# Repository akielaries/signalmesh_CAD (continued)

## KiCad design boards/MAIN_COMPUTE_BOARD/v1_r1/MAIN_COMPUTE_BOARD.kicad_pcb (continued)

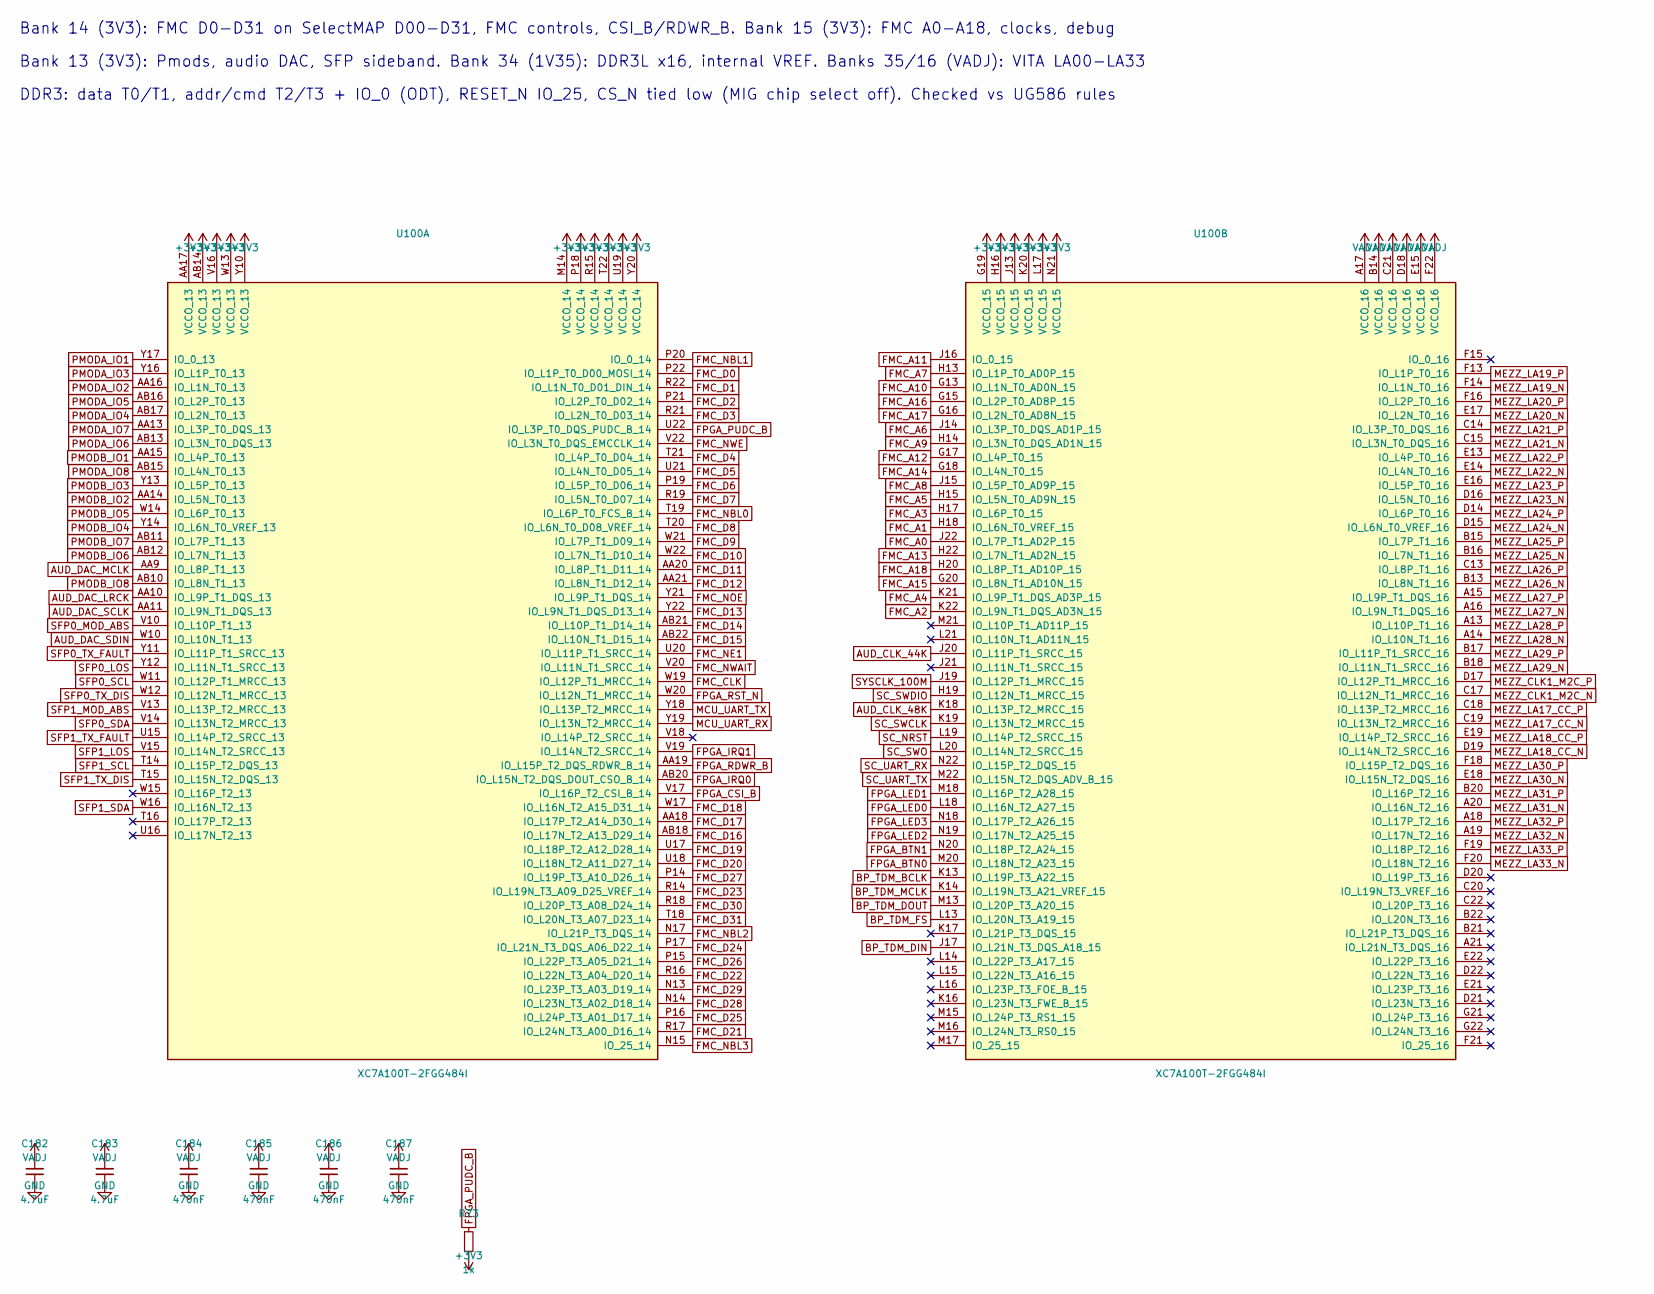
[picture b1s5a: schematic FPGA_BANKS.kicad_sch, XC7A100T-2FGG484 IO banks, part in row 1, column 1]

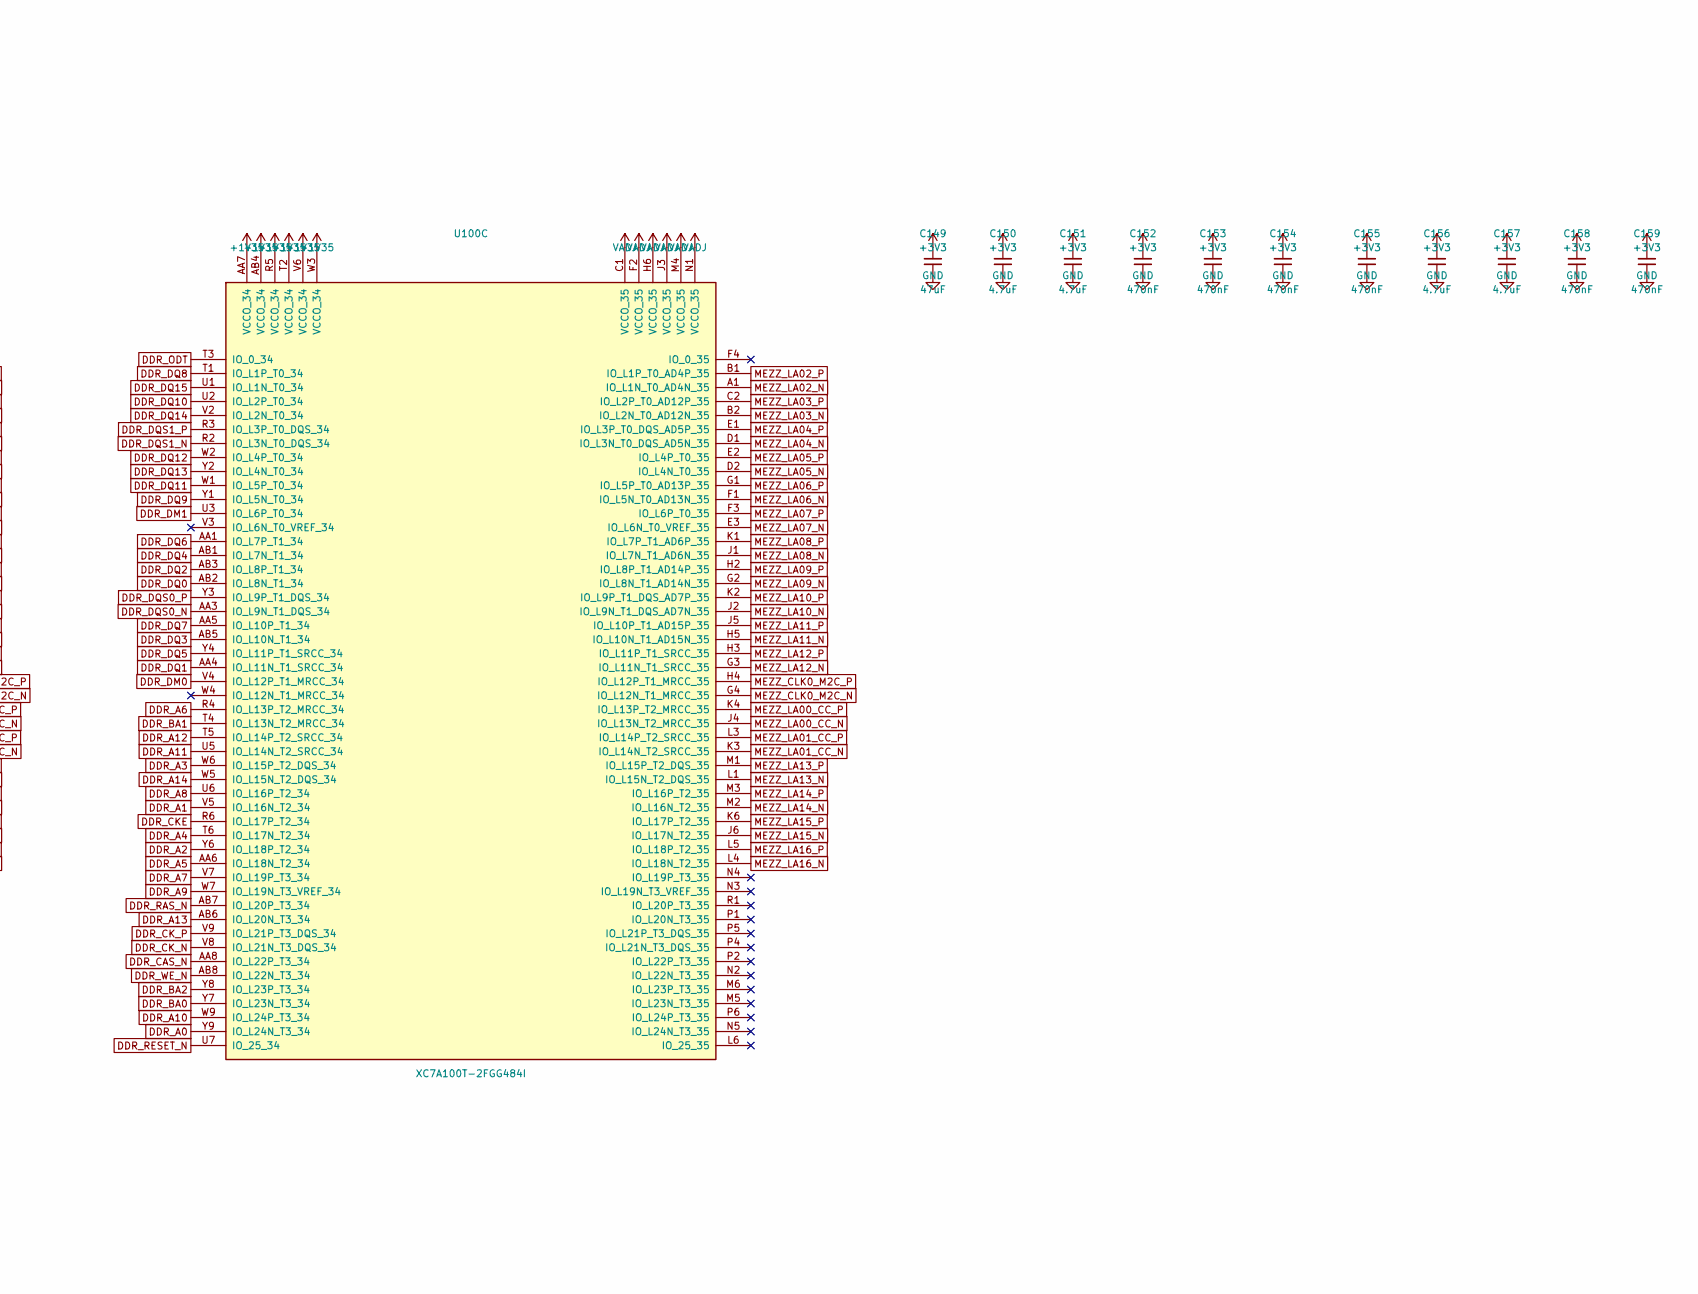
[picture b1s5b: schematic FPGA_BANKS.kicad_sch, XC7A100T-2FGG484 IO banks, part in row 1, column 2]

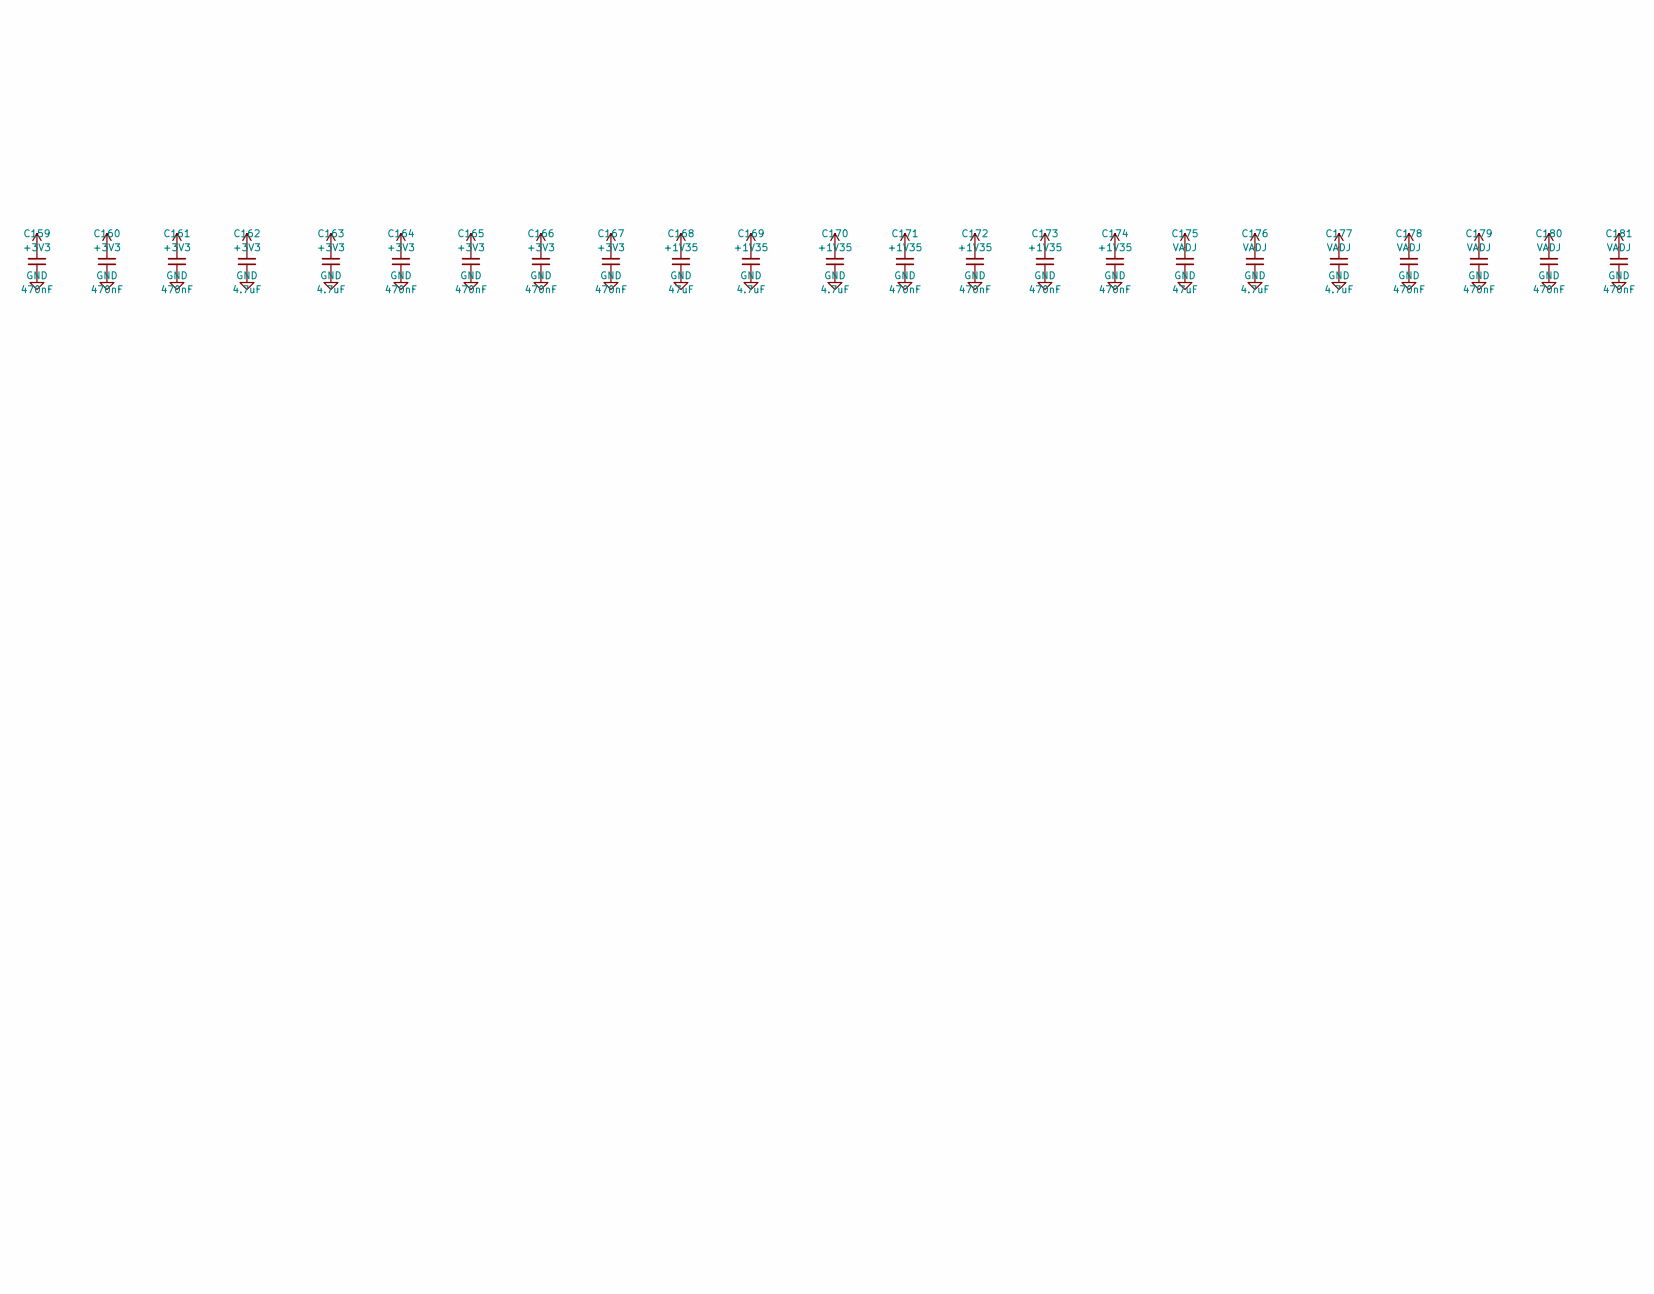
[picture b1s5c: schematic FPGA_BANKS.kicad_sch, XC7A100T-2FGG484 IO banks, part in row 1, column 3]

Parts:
C149, C168, C175: 47uF; C_1206_3216Metric
C150, C151, C156, C157, C162, C163, C169, C170, C176, C177, C182, C183: 4.7uF; C_0603_1608Metric
C152, C153, C154, C155, C158, C159, C160, C161, C164, C165, C166, C167, C171, C172, C173, C174, C178, C179, C180, C181, C184, C185, C186, C187: 470nF; C_0402_1005Metric
R73: 1k; R_0402_1005Metric
U100: XC7A100T-2FGG484I; Xilinx_FGG484

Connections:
+1V35: C168.1, C169.1, C170.1, C171.1, C172.1, C173.1, C174.1, U100.AA7 (VCCO_34), U100.AB4 (VCCO_34), U100.R5 (VCCO_34), U100.T2 (VCCO_34), U100.V6 (VCCO_34), U100.W3 (VCCO_34); also elsewhere on the board
+3V3: C149.1, C150.1, C151.1, C152.1, C153.1, C154.1, C155.1, C156.1, C157.1, C158.1, C159.1, C160.1, C161.1, C162.1, C163.1, C164.1, C165.1, C166.1, C167.1, R73.2, U100.AA17 (VCCO_13), U100.AB14 (VCCO_13), U100.G19 (VCCO_15), U100.H16 (VCCO_15), U100.J13 (VCCO_15), U100.K20 (VCCO_15), U100.L17 (VCCO_15), U100.M14 (VCCO_14), U100.N21 (VCCO_15), U100.P18 (VCCO_14), U100.R15 (VCCO_14), U100.T22 (VCCO_14), U100.U19 (VCCO_14), U100.V16 (VCCO_13), U100.W13 (VCCO_13), U100.Y10 (VCCO_13), U100.Y20 (VCCO_14); also elsewhere on the board
AUD_CLK_44K: U100.J20 (IO_L11P_T1_SRCC_15); also elsewhere on the board
AUD_CLK_48K: U100.K18 (IO_L13P_T2_MRCC_15); also elsewhere on the board
AUD_DAC_LRCK: U100.AA10 (IO_L9P_T1_DQS_13); also elsewhere on the board
AUD_DAC_MCLK: U100.AA9 (IO_L8P_T1_13); also elsewhere on the board
AUD_DAC_SCLK: U100.AA11 (IO_L9N_T1_DQS_13); also elsewhere on the board
AUD_DAC_SDIN: U100.W10 (IO_L10N_T1_13); also elsewhere on the board
BP_TDM_BCLK: U100.K13 (IO_L19P_T3_A22_15); also elsewhere on the board
BP_TDM_DIN: U100.J17 (IO_L21N_T3_DQS_A18_15); also elsewhere on the board
BP_TDM_DOUT: U100.M13 (IO_L20P_T3_A20_15); also elsewhere on the board
BP_TDM_FS: U100.L13 (IO_L20N_T3_A19_15); also elsewhere on the board
BP_TDM_MCLK: U100.K14 (IO_L19N_T3_A21_VREF_15); also elsewhere on the board
DDR_A0: U100.Y9 (IO_L24N_T3_34); also elsewhere on the board
DDR_A1: U100.V5 (IO_L16N_T2_34); also elsewhere on the board
DDR_A2: U100.Y6 (IO_L18P_T2_34); also elsewhere on the board
DDR_A3: U100.W6 (IO_L15P_T2_DQS_34); also elsewhere on the board
DDR_A4: U100.T6 (IO_L17N_T2_34); also elsewhere on the board
DDR_A5: U100.AA6 (IO_L18N_T2_34); also elsewhere on the board
DDR_A6: U100.R4 (IO_L13P_T2_MRCC_34); also elsewhere on the board
DDR_A7: U100.V7 (IO_L19P_T3_34); also elsewhere on the board
DDR_A8: U100.U6 (IO_L16P_T2_34); also elsewhere on the board
DDR_A9: U100.W7 (IO_L19N_T3_VREF_34); also elsewhere on the board
DDR_A10: U100.W9 (IO_L24P_T3_34); also elsewhere on the board
DDR_A11: U100.U5 (IO_L14N_T2_SRCC_34); also elsewhere on the board
DDR_A12: U100.T5 (IO_L14P_T2_SRCC_34); also elsewhere on the board
DDR_A13: U100.AB6 (IO_L20N_T3_34); also elsewhere on the board
DDR_A14: U100.W5 (IO_L15N_T2_DQS_34); also elsewhere on the board
DDR_BA0: U100.Y7 (IO_L23N_T3_34); also elsewhere on the board
DDR_BA1: U100.T4 (IO_L13N_T2_MRCC_34); also elsewhere on the board
DDR_BA2: U100.Y8 (IO_L23P_T3_34); also elsewhere on the board
DDR_CAS_N: U100.AA8 (IO_L22P_T3_34); also elsewhere on the board
DDR_CKE: U100.R6 (IO_L17P_T2_34); also elsewhere on the board
DDR_CK_N: U100.V8 (IO_L21N_T3_DQS_34); also elsewhere on the board
DDR_CK_P: U100.V9 (IO_L21P_T3_DQS_34); also elsewhere on the board
DDR_DM0: U100.V4 (IO_L12P_T1_MRCC_34); also elsewhere on the board
DDR_DM1: U100.U3 (IO_L6P_T0_34); also elsewhere on the board
DDR_DQ0: U100.AB2 (IO_L8N_T1_34); also elsewhere on the board
DDR_DQ1: U100.AA4 (IO_L11N_T1_SRCC_34); also elsewhere on the board
DDR_DQ2: U100.AB3 (IO_L8P_T1_34); also elsewhere on the board
DDR_DQ3: U100.AB5 (IO_L10N_T1_34); also elsewhere on the board
DDR_DQ4: U100.AB1 (IO_L7N_T1_34); also elsewhere on the board
DDR_DQ5: U100.Y4 (IO_L11P_T1_SRCC_34); also elsewhere on the board
DDR_DQ6: U100.AA1 (IO_L7P_T1_34); also elsewhere on the board
DDR_DQ7: U100.AA5 (IO_L10P_T1_34); also elsewhere on the board
DDR_DQ8: U100.T1 (IO_L1P_T0_34); also elsewhere on the board
DDR_DQ9: U100.Y1 (IO_L5N_T0_34); also elsewhere on the board
DDR_DQ10: U100.U2 (IO_L2P_T0_34); also elsewhere on the board
DDR_DQ11: U100.W1 (IO_L5P_T0_34); also elsewhere on the board
DDR_DQ12: U100.W2 (IO_L4P_T0_34); also elsewhere on the board
DDR_DQ13: U100.Y2 (IO_L4N_T0_34); also elsewhere on the board
DDR_DQ14: U100.V2 (IO_L2N_T0_34); also elsewhere on the board
DDR_DQ15: U100.U1 (IO_L1N_T0_34); also elsewhere on the board
DDR_DQS0_N: U100.AA3 (IO_L9N_T1_DQS_34); also elsewhere on the board
DDR_DQS0_P: U100.Y3 (IO_L9P_T1_DQS_34); also elsewhere on the board
DDR_DQS1_N: U100.R2 (IO_L3N_T0_DQS_34); also elsewhere on the board
DDR_DQS1_P: U100.R3 (IO_L3P_T0_DQS_34); also elsewhere on the board
DDR_ODT: U100.T3 (IO_0_34); also elsewhere on the board
DDR_RAS_N: U100.AB7 (IO_L20P_T3_34); also elsewhere on the board
DDR_RESET_N: U100.U7 (IO_25_34); also elsewhere on the board
DDR_WE_N: U100.AB8 (IO_L22N_T3_34); also elsewhere on the board
FMC_A0: U100.J22 (IO_L7P_T1_AD2P_15); also elsewhere on the board
FMC_A1: U100.H18 (IO_L6N_T0_VREF_15); also elsewhere on the board
FMC_A2: U100.K22 (IO_L9N_T1_DQS_AD3N_15); also elsewhere on the board
FMC_A3: U100.H17 (IO_L6P_T0_15); also elsewhere on the board
FMC_A4: U100.K21 (IO_L9P_T1_DQS_AD3P_15); also elsewhere on the board
FMC_A5: U100.H15 (IO_L5N_T0_AD9N_15); also elsewhere on the board
FMC_A6: U100.J14 (IO_L3P_T0_DQS_AD1P_15); also elsewhere on the board
FMC_A7: U100.H13 (IO_L1P_T0_AD0P_15); also elsewhere on the board
FMC_A8: U100.J15 (IO_L5P_T0_AD9P_15); also elsewhere on the board
FMC_A9: U100.H14 (IO_L3N_T0_DQS_AD1N_15); also elsewhere on the board
FMC_A10: U100.G13 (IO_L1N_T0_AD0N_15); also elsewhere on the board
FMC_A11: U100.J16 (IO_0_15); also elsewhere on the board
FMC_A12: U100.G17 (IO_L4P_T0_15); also elsewhere on the board
FMC_A13: U100.H22 (IO_L7N_T1_AD2N_15); also elsewhere on the board
FMC_A14: U100.G18 (IO_L4N_T0_15); also elsewhere on the board
FMC_A15: U100.G20 (IO_L8N_T1_AD10N_15); also elsewhere on the board
FMC_A16: U100.G15 (IO_L2P_T0_AD8P_15); also elsewhere on the board
FMC_A17: U100.G16 (IO_L2N_T0_AD8N_15); also elsewhere on the board
FMC_A18: U100.H20 (IO_L8P_T1_AD10P_15); also elsewhere on the board
FMC_CLK: U100.W19 (IO_L12P_T1_MRCC_14); also elsewhere on the board
FMC_D0: U100.P22 (IO_L1P_T0_D00_MOSI_14); also elsewhere on the board
FMC_D1: U100.R22 (IO_L1N_T0_D01_DIN_14); also elsewhere on the board
FMC_D2: U100.P21 (IO_L2P_T0_D02_14); also elsewhere on the board
FMC_D3: U100.R21 (IO_L2N_T0_D03_14); also elsewhere on the board
FMC_D4: U100.T21 (IO_L4P_T0_D04_14); also elsewhere on the board
FMC_D5: U100.U21 (IO_L4N_T0_D05_14); also elsewhere on the board
FMC_D6: U100.P19 (IO_L5P_T0_D06_14); also elsewhere on the board
FMC_D7: U100.R19 (IO_L5N_T0_D07_14); also elsewhere on the board
FMC_D8: U100.T20 (IO_L6N_T0_D08_VREF_14); also elsewhere on the board
FMC_D9: U100.W21 (IO_L7P_T1_D09_14); also elsewhere on the board
FMC_D10: U100.W22 (IO_L7N_T1_D10_14); also elsewhere on the board
FMC_D11: U100.AA20 (IO_L8P_T1_D11_14); also elsewhere on the board
FMC_D12: U100.AA21 (IO_L8N_T1_D12_14); also elsewhere on the board
FMC_D13: U100.Y22 (IO_L9N_T1_DQS_D13_14); also elsewhere on the board
FMC_D14: U100.AB21 (IO_L10P_T1_D14_14); also elsewhere on the board
FMC_D15: U100.AB22 (IO_L10N_T1_D15_14); also elsewhere on the board
FMC_D16: U100.AB18 (IO_L17N_T2_A13_D29_14); also elsewhere on the board
FMC_D17: U100.AA18 (IO_L17P_T2_A14_D30_14); also elsewhere on the board
FMC_D18: U100.W17 (IO_L16N_T2_A15_D31_14); also elsewhere on the board
FMC_D19: U100.U17 (IO_L18P_T2_A12_D28_14); also elsewhere on the board
FMC_D20: U100.U18 (IO_L18N_T2_A11_D27_14); also elsewhere on the board
FMC_D21: U100.R17 (IO_L24N_T3_A00_D16_14); also elsewhere on the board
FMC_D22: U100.R16 (IO_L22N_T3_A04_D20_14); also elsewhere on the board
FMC_D23: U100.R14 (IO_L19N_T3_A09_D25_VREF_14); also elsewhere on the board
FMC_D24: U100.P17 (IO_L21N_T3_DQS_A06_D22_14); also elsewhere on the board
FMC_D25: U100.P16 (IO_L24P_T3_A01_D17_14); also elsewhere on the board
FMC_D26: U100.P15 (IO_L22P_T3_A05_D21_14); also elsewhere on the board
FMC_D27: U100.P14 (IO_L19P_T3_A10_D26_14); also elsewhere on the board
FMC_D28: U100.N14 (IO_L23N_T3_A02_D18_14); also elsewhere on the board
FMC_D29: U100.N13 (IO_L23P_T3_A03_D19_14); also elsewhere on the board
FMC_D30: U100.R18 (IO_L20P_T3_A08_D24_14); also elsewhere on the board
FMC_D31: U100.T18 (IO_L20N_T3_A07_D23_14); also elsewhere on the board
FMC_NBL0: U100.T19 (IO_L6P_T0_FCS_B_14); also elsewhere on the board
FMC_NBL1: U100.P20 (IO_0_14); also elsewhere on the board
FMC_NBL2: U100.N17 (IO_L21P_T3_DQS_14); also elsewhere on the board
FMC_NBL3: U100.N15 (IO_25_14); also elsewhere on the board
FMC_NE1: U100.U20 (IO_L11P_T1_SRCC_14); also elsewhere on the board
FMC_NOE: U100.Y21 (IO_L9P_T1_DQS_14); also elsewhere on the board
FMC_NWAIT: U100.V20 (IO_L11N_T1_SRCC_14); also elsewhere on the board
FMC_NWE: U100.V22 (IO_L3N_T0_DQS_EMCCLK_14); also elsewhere on the board
FPGA_BTN0: U100.M20 (IO_L18N_T2_A23_15); also elsewhere on the board
FPGA_BTN1: U100.N20 (IO_L18P_T2_A24_15); also elsewhere on the board
FPGA_CSI_B: U100.V17 (IO_L16P_T2_CSI_B_14); also elsewhere on the board
FPGA_IRQ0: U100.AB20 (IO_L15N_T2_DQS_DOUT_CSO_B_14); also elsewhere on the board
FPGA_IRQ1: U100.V19 (IO_L14N_T2_SRCC_14); also elsewhere on the board
FPGA_LED0: U100.L18 (IO_L16N_T2_A27_15); also elsewhere on the board
FPGA_LED1: U100.M18 (IO_L16P_T2_A28_15); also elsewhere on the board
FPGA_LED2: U100.N19 (IO_L17N_T2_A25_15); also elsewhere on the board
FPGA_LED3: U100.N18 (IO_L17P_T2_A26_15); also elsewhere on the board
FPGA_PUDC_B: R73.1, U100.U22 (IO_L3P_T0_DQS_PUDC_B_14)
FPGA_RDWR_B: U100.AA19 (IO_L15P_T2_DQS_RDWR_B_14); also elsewhere on the board
FPGA_RST_N: U100.W20 (IO_L12N_T1_MRCC_14); also elsewhere on the board
GND: C149.2, C150.2, C151.2, C152.2, C153.2, C154.2, C155.2, C156.2, C157.2, C158.2, C159.2, C160.2, C161.2, C162.2, C163.2, C164.2, C165.2, C166.2, C167.2, C168.2, C169.2, C170.2, C171.2, C172.2, C173.2, C174.2, C175.2, C176.2, C177.2, C178.2, C179.2, C180.2, C181.2, C182.2, C183.2, C184.2, C185.2, C186.2, C187.2; also elsewhere on the board
MCU_UART_RX: U100.Y19 (IO_L13N_T2_MRCC_14); also elsewhere on the board
MCU_UART_TX: U100.Y18 (IO_L13P_T2_MRCC_14); also elsewhere on the board
MEZZ_CLK0_M2C_N: U100.G4 (IO_L12N_T1_MRCC_35); also elsewhere on the board
MEZZ_CLK0_M2C_P: U100.H4 (IO_L12P_T1_MRCC_35); also elsewhere on the board
MEZZ_CLK1_M2C_N: U100.C17 (IO_L12N_T1_MRCC_16); also elsewhere on the board
MEZZ_CLK1_M2C_P: U100.D17 (IO_L12P_T1_MRCC_16); also elsewhere on the board
MEZZ_LA00_CC_N: U100.J4 (IO_L13N_T2_MRCC_35); also elsewhere on the board
MEZZ_LA00_CC_P: U100.K4 (IO_L13P_T2_MRCC_35); also elsewhere on the board
MEZZ_LA01_CC_N: U100.K3 (IO_L14N_T2_SRCC_35); also elsewhere on the board
MEZZ_LA01_CC_P: U100.L3 (IO_L14P_T2_SRCC_35); also elsewhere on the board
MEZZ_LA02_N: U100.A1 (IO_L1N_T0_AD4N_35); also elsewhere on the board
MEZZ_LA02_P: U100.B1 (IO_L1P_T0_AD4P_35); also elsewhere on the board
MEZZ_LA03_N: U100.B2 (IO_L2N_T0_AD12N_35); also elsewhere on the board
MEZZ_LA03_P: U100.C2 (IO_L2P_T0_AD12P_35); also elsewhere on the board
MEZZ_LA04_N: U100.D1 (IO_L3N_T0_DQS_AD5N_35); also elsewhere on the board
MEZZ_LA04_P: U100.E1 (IO_L3P_T0_DQS_AD5P_35); also elsewhere on the board
MEZZ_LA05_N: U100.D2 (IO_L4N_T0_35); also elsewhere on the board
MEZZ_LA05_P: U100.E2 (IO_L4P_T0_35); also elsewhere on the board
MEZZ_LA06_N: U100.F1 (IO_L5N_T0_AD13N_35); also elsewhere on the board
MEZZ_LA06_P: U100.G1 (IO_L5P_T0_AD13P_35); also elsewhere on the board
MEZZ_LA07_N: U100.E3 (IO_L6N_T0_VREF_35); also elsewhere on the board
MEZZ_LA07_P: U100.F3 (IO_L6P_T0_35); also elsewhere on the board
MEZZ_LA08_N: U100.J1 (IO_L7N_T1_AD6N_35); also elsewhere on the board
MEZZ_LA08_P: U100.K1 (IO_L7P_T1_AD6P_35); also elsewhere on the board
MEZZ_LA09_N: U100.G2 (IO_L8N_T1_AD14N_35); also elsewhere on the board
MEZZ_LA09_P: U100.H2 (IO_L8P_T1_AD14P_35); also elsewhere on the board
MEZZ_LA10_N: U100.J2 (IO_L9N_T1_DQS_AD7N_35); also elsewhere on the board
MEZZ_LA10_P: U100.K2 (IO_L9P_T1_DQS_AD7P_35); also elsewhere on the board
MEZZ_LA11_N: U100.H5 (IO_L10N_T1_AD15N_35); also elsewhere on the board
MEZZ_LA11_P: U100.J5 (IO_L10P_T1_AD15P_35); also elsewhere on the board
MEZZ_LA12_N: U100.G3 (IO_L11N_T1_SRCC_35); also elsewhere on the board
MEZZ_LA12_P: U100.H3 (IO_L11P_T1_SRCC_35); also elsewhere on the board
MEZZ_LA13_N: U100.L1 (IO_L15N_T2_DQS_35); also elsewhere on the board
MEZZ_LA13_P: U100.M1 (IO_L15P_T2_DQS_35); also elsewhere on the board
MEZZ_LA14_N: U100.M2 (IO_L16N_T2_35); also elsewhere on the board
MEZZ_LA14_P: U100.M3 (IO_L16P_T2_35); also elsewhere on the board
MEZZ_LA15_N: U100.J6 (IO_L17N_T2_35); also elsewhere on the board
MEZZ_LA15_P: U100.K6 (IO_L17P_T2_35); also elsewhere on the board
MEZZ_LA16_N: U100.L4 (IO_L18N_T2_35); also elsewhere on the board
MEZZ_LA16_P: U100.L5 (IO_L18P_T2_35); also elsewhere on the board
MEZZ_LA17_CC_N: U100.C19 (IO_L13N_T2_MRCC_16); also elsewhere on the board
MEZZ_LA17_CC_P: U100.C18 (IO_L13P_T2_MRCC_16); also elsewhere on the board
MEZZ_LA18_CC_N: U100.D19 (IO_L14N_T2_SRCC_16); also elsewhere on the board
MEZZ_LA18_CC_P: U100.E19 (IO_L14P_T2_SRCC_16); also elsewhere on the board
MEZZ_LA19_N: U100.F14 (IO_L1N_T0_16); also elsewhere on the board
MEZZ_LA19_P: U100.F13 (IO_L1P_T0_16); also elsewhere on the board
MEZZ_LA20_N: U100.E17 (IO_L2N_T0_16); also elsewhere on the board
MEZZ_LA20_P: U100.F16 (IO_L2P_T0_16); also elsewhere on the board
MEZZ_LA21_N: U100.C15 (IO_L3N_T0_DQS_16); also elsewhere on the board
MEZZ_LA21_P: U100.C14 (IO_L3P_T0_DQS_16); also elsewhere on the board
MEZZ_LA22_N: U100.E14 (IO_L4N_T0_16); also elsewhere on the board
MEZZ_LA22_P: U100.E13 (IO_L4P_T0_16); also elsewhere on the board
MEZZ_LA23_N: U100.D16 (IO_L5N_T0_16); also elsewhere on the board
MEZZ_LA23_P: U100.E16 (IO_L5P_T0_16); also elsewhere on the board
MEZZ_LA24_N: U100.D15 (IO_L6N_T0_VREF_16); also elsewhere on the board
MEZZ_LA24_P: U100.D14 (IO_L6P_T0_16); also elsewhere on the board
MEZZ_LA25_N: U100.B16 (IO_L7N_T1_16); also elsewhere on the board
MEZZ_LA25_P: U100.B15 (IO_L7P_T1_16); also elsewhere on the board
MEZZ_LA26_N: U100.B13 (IO_L8N_T1_16); also elsewhere on the board
MEZZ_LA26_P: U100.C13 (IO_L8P_T1_16); also elsewhere on the board
MEZZ_LA27_N: U100.A16 (IO_L9N_T1_DQS_16); also elsewhere on the board
MEZZ_LA27_P: U100.A15 (IO_L9P_T1_DQS_16); also elsewhere on the board
MEZZ_LA28_N: U100.A14 (IO_L10N_T1_16); also elsewhere on the board
MEZZ_LA28_P: U100.A13 (IO_L10P_T1_16); also elsewhere on the board
MEZZ_LA29_N: U100.B18 (IO_L11N_T1_SRCC_16); also elsewhere on the board
MEZZ_LA29_P: U100.B17 (IO_L11P_T1_SRCC_16); also elsewhere on the board
MEZZ_LA30_N: U100.E18 (IO_L15N_T2_DQS_16); also elsewhere on the board
MEZZ_LA30_P: U100.F18 (IO_L15P_T2_DQS_16); also elsewhere on the board
MEZZ_LA31_N: U100.A20 (IO_L16N_T2_16); also elsewhere on the board
MEZZ_LA31_P: U100.B20 (IO_L16P_T2_16); also elsewhere on the board
MEZZ_LA32_N: U100.A19 (IO_L17N_T2_16); also elsewhere on the board
MEZZ_LA32_P: U100.A18 (IO_L17P_T2_16); also elsewhere on the board
MEZZ_LA33_N: U100.F20 (IO_L18N_T2_16); also elsewhere on the board
MEZZ_LA33_P: U100.F19 (IO_L18P_T2_16); also elsewhere on the board
PMODA_IO1: U100.Y17 (IO_0_13); also elsewhere on the board
PMODA_IO2: U100.AA16 (IO_L1N_T0_13); also elsewhere on the board
PMODA_IO3: U100.Y16 (IO_L1P_T0_13); also elsewhere on the board
PMODA_IO4: U100.AB17 (IO_L2N_T0_13); also elsewhere on the board
PMODA_IO5: U100.AB16 (IO_L2P_T0_13); also elsewhere on the board
PMODA_IO6: U100.AB13 (IO_L3N_T0_DQS_13); also elsewhere on the board
PMODA_IO7: U100.AA13 (IO_L3P_T0_DQS_13); also elsewhere on the board
PMODA_IO8: U100.AB15 (IO_L4N_T0_13); also elsewhere on the board
PMODB_IO1: U100.AA15 (IO_L4P_T0_13); also elsewhere on the board
PMODB_IO2: U100.AA14 (IO_L5N_T0_13); also elsewhere on the board
PMODB_IO3: U100.Y13 (IO_L5P_T0_13); also elsewhere on the board
PMODB_IO4: U100.Y14 (IO_L6N_T0_VREF_13); also elsewhere on the board
PMODB_IO5: U100.W14 (IO_L6P_T0_13); also elsewhere on the board
PMODB_IO6: U100.AB12 (IO_L7N_T1_13); also elsewhere on the board
PMODB_IO7: U100.AB11 (IO_L7P_T1_13); also elsewhere on the board
PMODB_IO8: U100.AB10 (IO_L8N_T1_13); also elsewhere on the board
SC_NRST: U100.L19 (IO_L14P_T2_SRCC_15); also elsewhere on the board
SC_SWCLK: U100.K19 (IO_L13N_T2_MRCC_15); also elsewhere on the board
SC_SWDIO: U100.H19 (IO_L12N_T1_MRCC_15); also elsewhere on the board
SC_SWO: U100.L20 (IO_L14N_T2_SRCC_15); also elsewhere on the board
SC_UART_RX: U100.N22 (IO_L15P_T2_DQS_15); also elsewhere on the board
SC_UART_TX: U100.M22 (IO_L15N_T2_DQS_ADV_B_15); also elsewhere on the board
SFP0_LOS: U100.Y12 (IO_L11N_T1_SRCC_13); also elsewhere on the board
SFP0_MOD_ABS: U100.V10 (IO_L10P_T1_13); also elsewhere on the board
SFP0_SCL: U100.W11 (IO_L12P_T1_MRCC_13); also elsewhere on the board
SFP0_SDA: U100.V14 (IO_L13N_T2_MRCC_13); also elsewhere on the board
SFP0_TX_DIS: U100.W12 (IO_L12N_T1_MRCC_13); also elsewhere on the board
SFP0_TX_FAULT: U100.Y11 (IO_L11P_T1_SRCC_13); also elsewhere on the board
SFP1_LOS: U100.V15 (IO_L14N_T2_SRCC_13); also elsewhere on the board
SFP1_MOD_ABS: U100.V13 (IO_L13P_T2_MRCC_13); also elsewhere on the board
SFP1_SCL: U100.T14 (IO_L15P_T2_DQS_13); also elsewhere on the board
SFP1_SDA: U100.W16 (IO_L16N_T2_13); also elsewhere on the board
SFP1_TX_DIS: U100.T15 (IO_L15N_T2_DQS_13); also elsewhere on the board
SFP1_TX_FAULT: U100.U15 (IO_L14P_T2_SRCC_13); also elsewhere on the board
SYSCLK_100M: U100.J19 (IO_L12P_T1_MRCC_15); also elsewhere on the board
VADJ: C175.1, C176.1, C177.1, C178.1, C179.1, C180.1, C181.1, C182.1, C183.1, C184.1, C185.1, C186.1, C187.1, U100.A17 (VCCO_16), U100.B14 (VCCO_16), U100.C1 (VCCO_35), U100.C21 (VCCO_16), U100.D18 (VCCO_16), U100.E15 (VCCO_16), U100.F2 (VCCO_35), U100.F22 (VCCO_16), U100.H6 (VCCO_35), U100.J3 (VCCO_35), U100.M4 (VCCO_35), U100.N1 (VCCO_35); also elsewhere on the board

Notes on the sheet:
Bank 14 (3V3): FMC D0-D31 on SelectMAP D00-D31, FMC controls, CSI_B/RDWR_B. Bank 15 (3V3): FMC A0-A18, clocks, debug
Bank 13 (3V3): Pmods, audio DAC, SFP sideband. Bank 34 (1V35): DDR3L x16, internal VREF. Banks 35/16 (VADJ): VITA LA00-LA33
DDR3: data T0/T1, addr/cmd T2/T3 + IO_0 (ODT), RESET_N IO_25, CS_N tied low (MIG chip select off). Checked vs UG586 rules

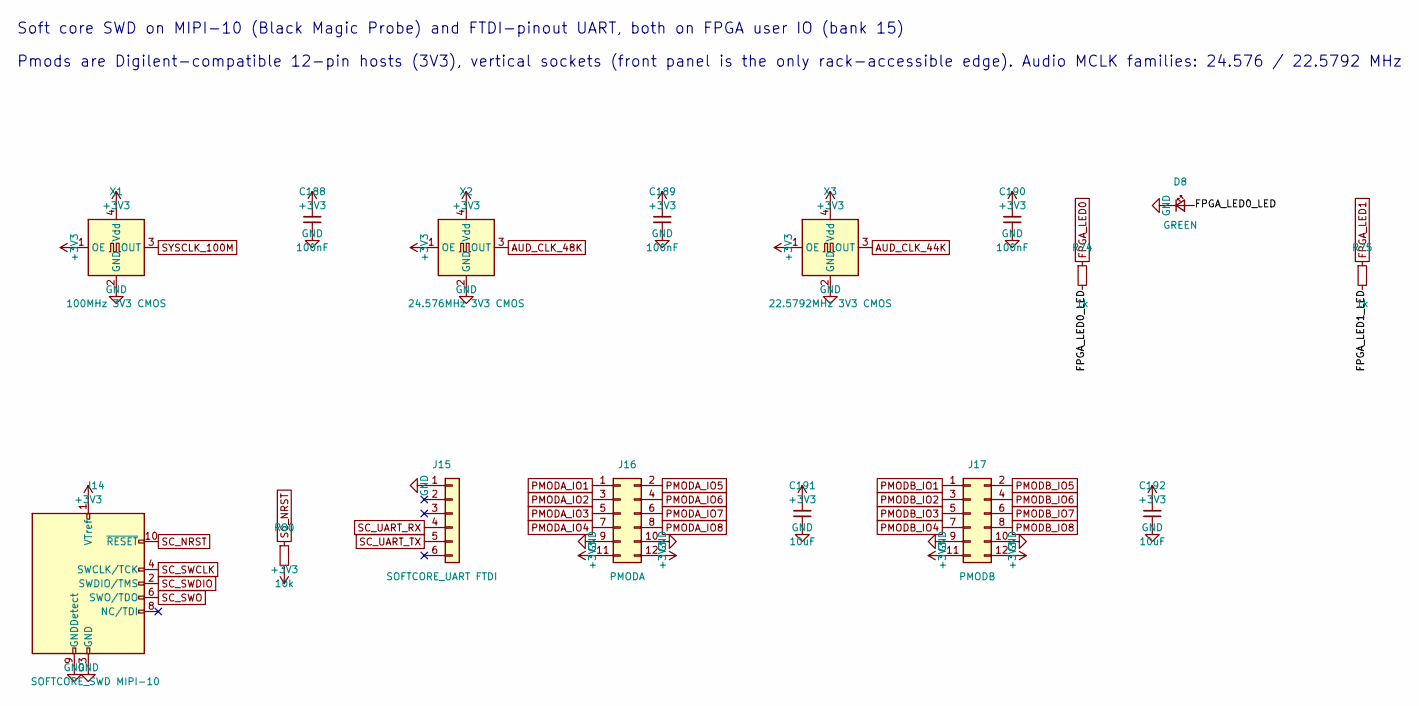
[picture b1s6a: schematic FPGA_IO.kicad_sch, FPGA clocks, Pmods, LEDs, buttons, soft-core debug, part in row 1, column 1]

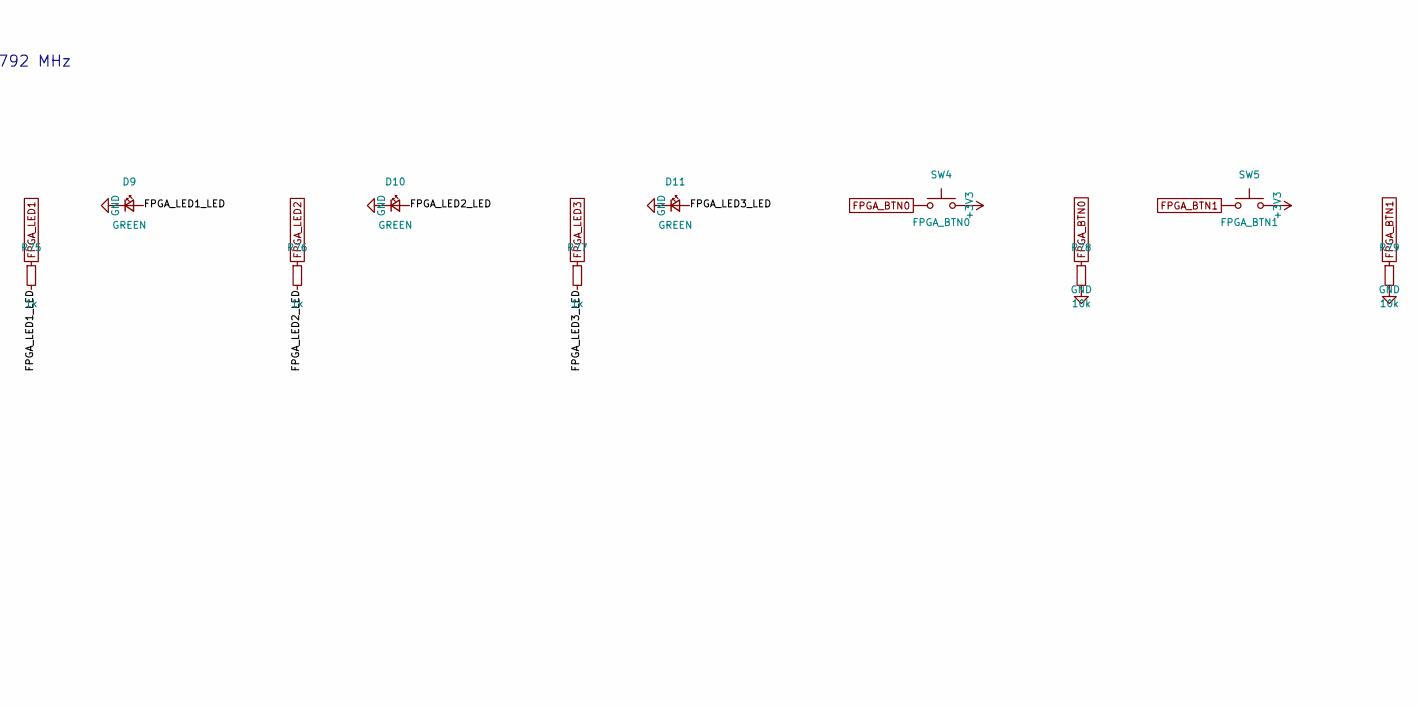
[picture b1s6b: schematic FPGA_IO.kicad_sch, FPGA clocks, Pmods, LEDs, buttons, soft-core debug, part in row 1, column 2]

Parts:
C188, C189, C190: 100nF; C_0402_1005Metric
C191, C192: 10uF; C_0805_2012Metric
D8, D9, D10, D11: GREEN; LED_0603_1608Metric
J14: SOFTCORE_SWD MIPI-10; PinHeader_2x05_P1.27mm_Vertical_SMD
J15: SOFTCORE_UART FTDI; PinHeader_1x06_P2.54mm_Vertical
J16: PMODA; PinSocket_2x06_P2.54mm_Vertical
J17: PMODB; PinSocket_2x06_P2.54mm_Vertical
R74, R75, R76, R77: 1k; R_0402_1005Metric
R78, R79, R80: 10k; R_0402_1005Metric
SW4: FPGA_BTN0; SW_SPST_TL3342
SW5: FPGA_BTN1; SW_SPST_TL3342
X1: 100MHz 3V3 CMOS; Oscillator_SMD_Abracon_ASE-4Pin_3.2x2.5mm
X2: 24.576MHz 3V3 CMOS; Oscillator_SMD_Abracon_ASE-4Pin_3.2x2.5mm
X3: 22.5792MHz 3V3 CMOS; Oscillator_SMD_Abracon_ASE-4Pin_3.2x2.5mm

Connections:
+3V3: C188.1, C189.1, C190.1, C191.1, C192.1, J14.1 (VTref), J16.11, J16.12, J17.11, J17.12, R80.2, SW4.2, SW5.2, X1.1 (OE), X1.4 (Vdd), X2.1 (OE), X2.4 (Vdd), X3.1 (OE), X3.4 (Vdd); also elsewhere on the board
/FPGA_IO/FPGA_LED0_LED: D8.2 (A), R74.2
/FPGA_IO/FPGA_LED1_LED: D9.2 (A), R75.2
/FPGA_IO/FPGA_LED2_LED: D10.2 (A), R76.2
/FPGA_IO/FPGA_LED3_LED: D11.2 (A), R77.2
AUD_CLK_44K: X3.3 (OUT); also elsewhere on the board
AUD_CLK_48K: X2.3 (OUT); also elsewhere on the board
FPGA_BTN0: R78.1, SW4.1; also elsewhere on the board
FPGA_BTN1: R79.1, SW5.1; also elsewhere on the board
FPGA_LED0: R74.1; also elsewhere on the board
FPGA_LED1: R75.1; also elsewhere on the board
FPGA_LED2: R76.1; also elsewhere on the board
FPGA_LED3: R77.1; also elsewhere on the board
GND: C188.2, C189.2, C190.2, C191.2, C192.2, D8.1 (K), D9.1 (K), D10.1 (K), D11.1 (K), J14.3 (GND), J14.5 (GND), J14.9 (GNDDetect), J15.1, J16.9, J16.10, J17.9, J17.10, R78.2, R79.2, X1.2 (GND), X2.2 (GND), X3.2 (GND); also elsewhere on the board
PMODA_IO1: J16.1; also elsewhere on the board
PMODA_IO2: J16.3; also elsewhere on the board
PMODA_IO3: J16.5; also elsewhere on the board
PMODA_IO4: J16.7; also elsewhere on the board
PMODA_IO5: J16.2; also elsewhere on the board
PMODA_IO6: J16.4; also elsewhere on the board
PMODA_IO7: J16.6; also elsewhere on the board
PMODA_IO8: J16.8; also elsewhere on the board
PMODB_IO1: J17.1; also elsewhere on the board
PMODB_IO2: J17.3; also elsewhere on the board
PMODB_IO3: J17.5; also elsewhere on the board
PMODB_IO4: J17.7; also elsewhere on the board
PMODB_IO5: J17.2; also elsewhere on the board
PMODB_IO6: J17.4; also elsewhere on the board
PMODB_IO7: J17.6; also elsewhere on the board
PMODB_IO8: J17.8; also elsewhere on the board
SC_NRST: J14.10 (~RESET), R80.1; also elsewhere on the board
SC_SWCLK: J14.4 (SWCLK/TCK); also elsewhere on the board
SC_SWDIO: J14.2 (SWDIO/TMS); also elsewhere on the board
SC_SWO: J14.6 (SWO/TDO); also elsewhere on the board
SC_UART_RX: J15.4; also elsewhere on the board
SC_UART_TX: J15.5; also elsewhere on the board
SYSCLK_100M: X1.3 (OUT); also elsewhere on the board

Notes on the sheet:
Soft core SWD on MIPI-10 (Black Magic Probe) and FTDI-pinout UART, both on FPGA user IO (bank 15)
Pmods are Digilent-compatible 12-pin hosts (3V3), vertical sockets (front panel is the only rack-accessible edge). Audio MCLK families: 24.576 / 22.5792 MHz
